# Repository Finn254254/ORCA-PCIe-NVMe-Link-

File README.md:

# ORCA PCIe NVMe Link

ORCA PCIe NVMe Link is a custom PCIe expansion board designed by Finn and branded ORCA Servers. It is intended to add M.2 NVMe storage through a PCIe x4 interface as part of the modular ORCA hardware platform.

## Support ORCA development

The design work is complete enough to prepare for prototyping, but physical manufacturing, assembly, independent engineering review and hardware testing still need funding.

If you want to help move ORCA from design files to a tested physical prototype:

**[Support ORCA on Buy Me a Coffee](https://buymeacoffee.com/finnmather)**

Support will be put toward prototype PCB fabrication, connectors and components, assembly, electrical and signal-integrity review, compatibility testing, and documentation. Progress and testing results will be documented in this repository.

Contributions are voluntary support for development. They are not pre-orders, investments, equity, or guarantees that finished hardware will be delivered.

## Features

- PCIe x4 host interface
- M.2 NVMe storage support
- Compact, modular storage expansion for the ORCA hardware platform
- Custom hardware design intended for further development and testing

## Project status

This project is in development. The design has not yet been represented as production-ready, and specifications, layout, and documentation may change.

## Repository contents

- `README.md` — project overview, current status, manufacturing warning, and rights notice
- `images/` — PCB renders, layout views, and a schematic overview
- `hardware/` — KiCad schematic and PCB source files, plus the BOM CSV

Additional design, fabrication, and supporting files may be added as the project develops.

## Design gallery

### PCB renders

| Front | Back |
| --- | --- |
|  |  |

### PCB layout

| Top | Bottom |
| --- | --- |
|  |  |

### Schematic overview

## Bill of Materials

The full machine-readable BOM is available at [`hardware/BOM.csv`](hardware/BOM.csv).

| Reference | Qty | Value / part | Footprint |
| --- | ---: | --- | --- |
| C1 | 1 | 10uF | 0805 SMD capacitor |
| C2 | 1 | 100nF | 0402 SMD capacitor |
| C3 | 1 | 22uF | 0805 SMD capacitor |
| D1 | 1 | LED | 0603 SMD LED |
| F1 | 1 | 3A fuse | 1206 SMD fuse |
| J1 | 1 | PCIe x4 edge connector | PCIe x4 PCB edge |
| J2 | 1 | M.2 M-key socket | TE 1-2199119-5 |
| R1 | 1 | 1K | 0603 SMD resistor |

## Hardware source files

- [`ORCA PCIe NVMe Link V3.0.kicad_sch`](hardware/ORCA%20PCIe%20NVMe%20Link%20V3.0.kicad_sch) — KiCad schematic source
- [`ORCA PCIe NVMe Link V3.0.kicad_pcb`](hardware/ORCA%20PCIe%20NVMe%20Link%20V3.0.kicad_pcb) — KiCad PCB layout source

## Manufacturing warning

Do not manufacture, assemble, sell, or rely on this hardware without an independent engineering review and appropriate electrical, signal-integrity, thermal, safety, and compatibility testing. Prototype hardware may contain errors and could damage connected equipment or storage devices. Manufacturing is also restricted by the rights notice below.

## Rights

This design was personally created by Finn and is branded ORCA Servers.

Copyright © 2026 Finn, trading as ORCA Servers. All rights reserved. No permission is granted to copy, modify, redistribute, manufacture, sell, or create derivative works from this design without prior written permission.

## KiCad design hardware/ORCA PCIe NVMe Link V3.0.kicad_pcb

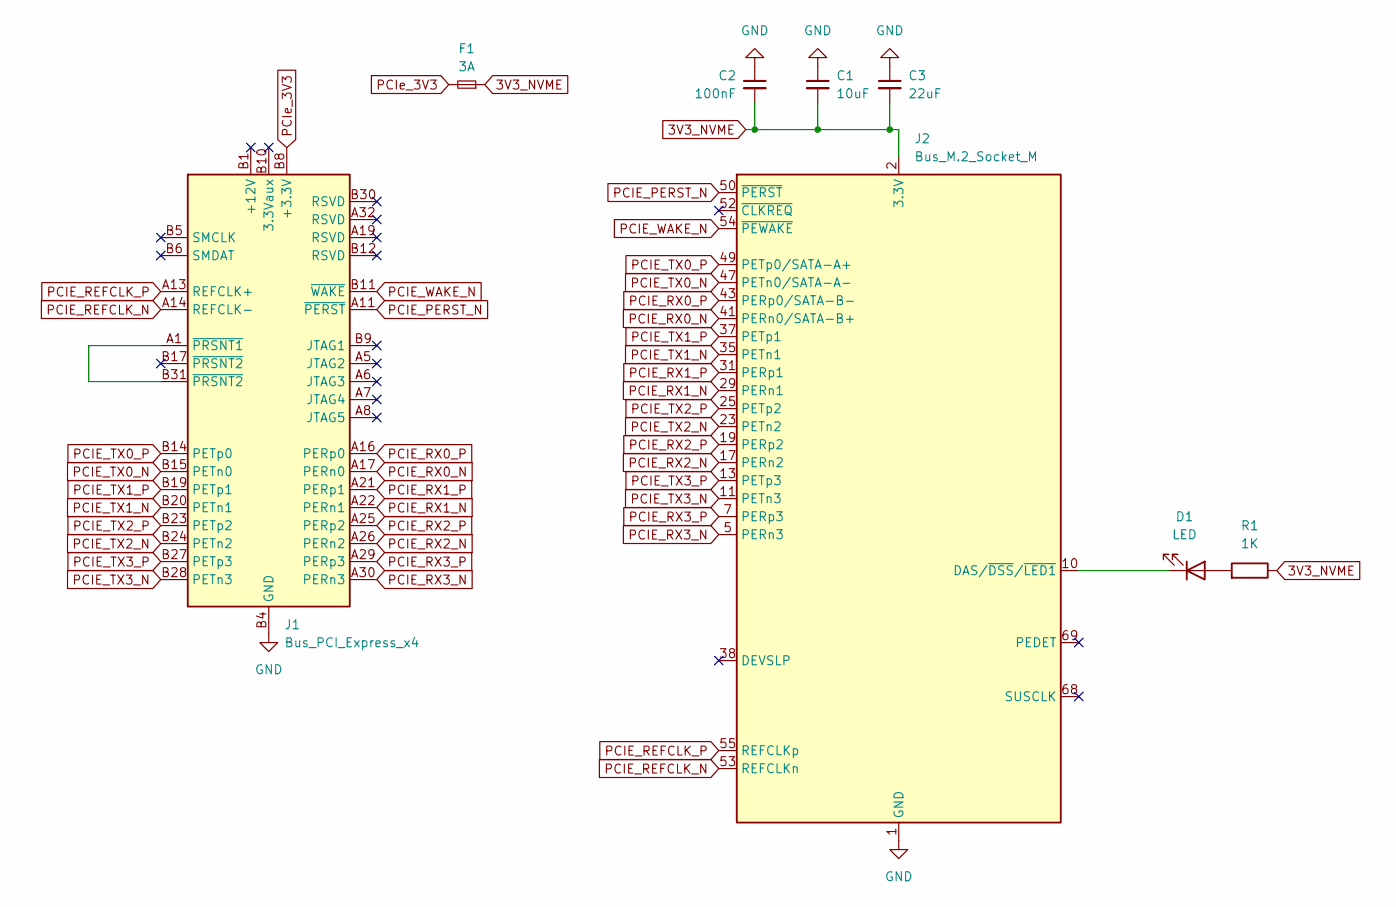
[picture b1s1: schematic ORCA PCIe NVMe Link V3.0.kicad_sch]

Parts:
C1: 10uF; C_0805_2012Metric
C2: 100nF; C_0402_1005Metric
C3: 22uF; C_0805_2012Metric
D1: LED; LED_0603_1608Metric
F1: 3A; Fuse_1206_3216Metric
J1: Bus_PCI_Express_x4; BUS_PCIexpress_x4
J2: Bus_M.2_Socket_M; TE_1-2199119-5
R1: 1K; R_0603_1608Metric

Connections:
3V3_NVME: C1.2, C2.2, C3.2, F1.1, J2.2 (3.3V), J2.4 (3.3V), J2.12 (3.3V), J2.14 (3.3V), J2.16 (3.3V), J2.18 (3.3V), J2.70 (3.3V), J2.72 (3.3V), J2.74 (3.3V), R1.1
GND: C1.1, C2.1, C3.1, J1.A4 (GND), J1.A12 (GND), J1.A15 (GND), J1.A18 (GND), J1.A20 (GND), J1.A23 (GND), J1.A24 (GND), J1.A27 (GND), J1.A28 (GND), J1.A31 (GND), J1.B4 (GND), J1.B7 (GND), J1.B13 (GND), J1.B16 (GND), J1.B18 (GND), J1.B21 (GND), J1.B22 (GND), J1.B25 (GND), J1.B26 (GND), J1.B29 (GND), J1.B32 (GND), J2.1 (GND), J2.3 (GND), J2.9 (GND), J2.15 (GND), J2.21 (GND), J2.27 (GND), J2.33 (GND), J2.39 (GND), J2.45 (GND), J2.51 (GND), J2.57 (GND), J2.71 (GND), J2.73 (GND), J2.75 (GND)
unnamed: D1.2 (A), R1.2
unnamed: D1.1 (K), J2.10 (DAS/~DSS/~LED1)
unnamed: J1.A1 (~PRSNT1), J1.B31 (~PRSNT2)
PCIE_PERST_N: J1.A11 (~PERST), J2.50 (~PERST)
PCIE_REFCLK_N: J1.A14 (REFCLK-), J2.53 (REFCLKn)
PCIE_REFCLK_P: J1.A13 (REFCLK+), J2.55 (REFCLKp)
PCIE_RX0_N: J1.A17 (PERn0), J2.41 (PERn0/SATA-B+)
PCIE_RX0_P: J1.A16 (PERp0), J2.43 (PERp0/SATA-B-)
PCIE_RX1_N: J1.A22 (PERn1), J2.29 (PERn1)
PCIE_RX1_P: J1.A21 (PERp1), J2.31 (PERp1)
PCIE_RX2_N: J1.A26 (PERn2), J2.17 (PERn2)
PCIE_RX2_P: J1.A25 (PERp2), J2.19 (PERp2)
PCIE_RX3_N: J1.A30 (PERn3), J2.5 (PERn3)
PCIE_RX3_P: J1.A29 (PERp3), J2.7 (PERp3)
PCIE_TX0_N: J1.B15 (PETn0), J2.47 (PETn0/SATA-A-)
PCIE_TX0_P: J1.B14 (PETp0), J2.49 (PETp0/SATA-A+)
PCIE_TX1_N: J1.B20 (PETn1), J2.35 (PETn1)
PCIE_TX1_P: J1.B19 (PETp1), J2.37 (PETp1)
PCIE_TX2_N: J1.B24 (PETn2), J2.23 (PETn2)
PCIE_TX2_P: J1.B23 (PETp2), J2.25 (PETp2)
PCIE_TX3_N: J1.B28 (PETn3), J2.11 (PETn3)
PCIE_TX3_P: J1.B27 (PETp3), J2.13 (PETp3)
PCIE_WAKE_N: J1.B11 (~WAKE), J2.54 (~PEWAKE)
PCIe_3V3: F1.2, J1.A9 (+3.3V), J1.A10 (+3.3V), J1.B8 (+3.3V)

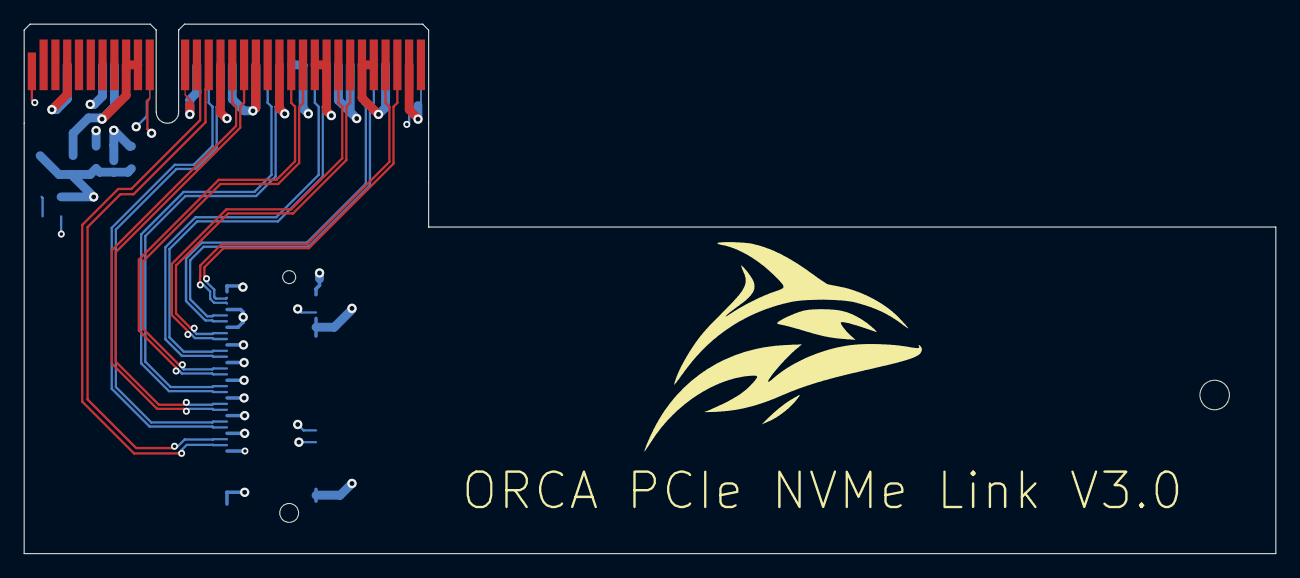
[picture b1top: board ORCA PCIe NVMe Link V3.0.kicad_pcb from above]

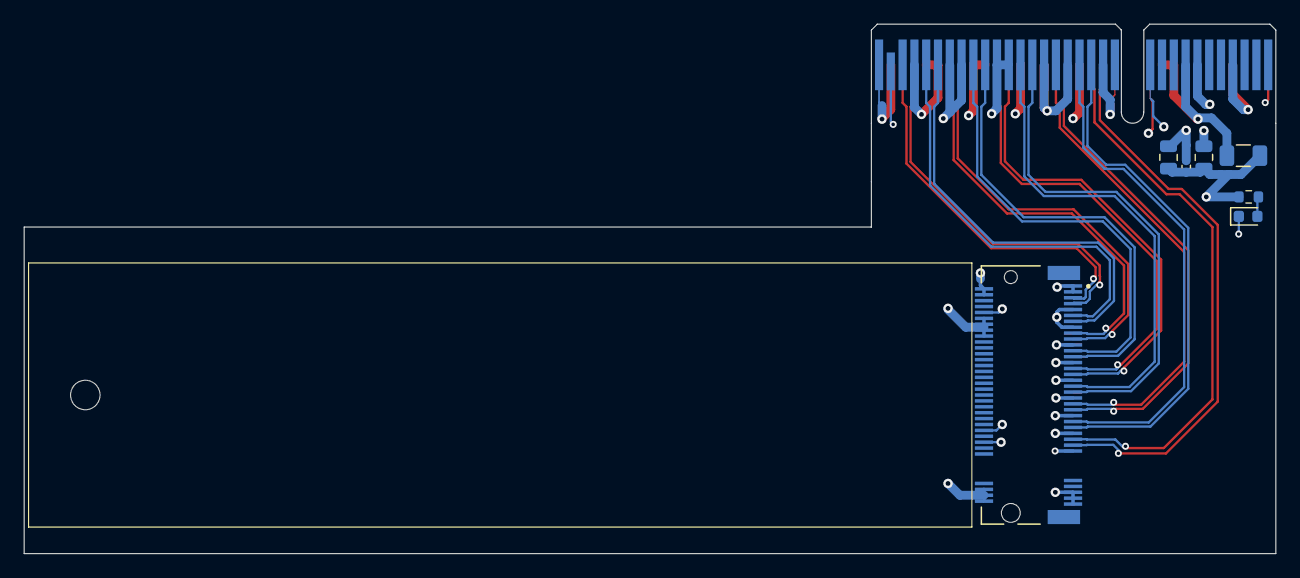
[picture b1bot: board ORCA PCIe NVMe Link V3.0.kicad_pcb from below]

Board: 6 copper layers, 106.2 x 44.9 mm, 9 parts (8 on the bottom side), 26 nets.

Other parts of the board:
2280: MountingHole_2.5mm

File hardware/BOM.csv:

"Reference","Qty","Value","DNP","Exclude from BOM","Exclude from Board","Footprint","Datasheet"
"C1","1","10uF","","","","Capacitor_SMD:C_0805_2012Metric","~"
"C2","1","100nF","","","","Capacitor_SMD:C_0402_1005Metric","~"
"C3","1","22uF","","","","Capacitor_SMD:C_0805_2012Metric","~"
"D1","1","LED","","","","LED_SMD:LED_0603_1608Metric","~"
"F1","1","3A","","","","Fuse:Fuse_1206_3216Metric","~"
"J1","1","Bus_PCI_Express_x4","","","","Connector_PCBEdge:BUS_PCIexpress_x4","http://www.ritrontek.com/uploadfile/2016/1026/20161026105231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"
"J2","1","Bus_M.2_Socket_M","","","","1-2199119-5:TE_1-2199119-5","https://web.archive.org/web/20200613074028/http://read.pudn.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"
"R1","1","1K","","","","Resistor_SMD:R_0603_1608Metric","~"
